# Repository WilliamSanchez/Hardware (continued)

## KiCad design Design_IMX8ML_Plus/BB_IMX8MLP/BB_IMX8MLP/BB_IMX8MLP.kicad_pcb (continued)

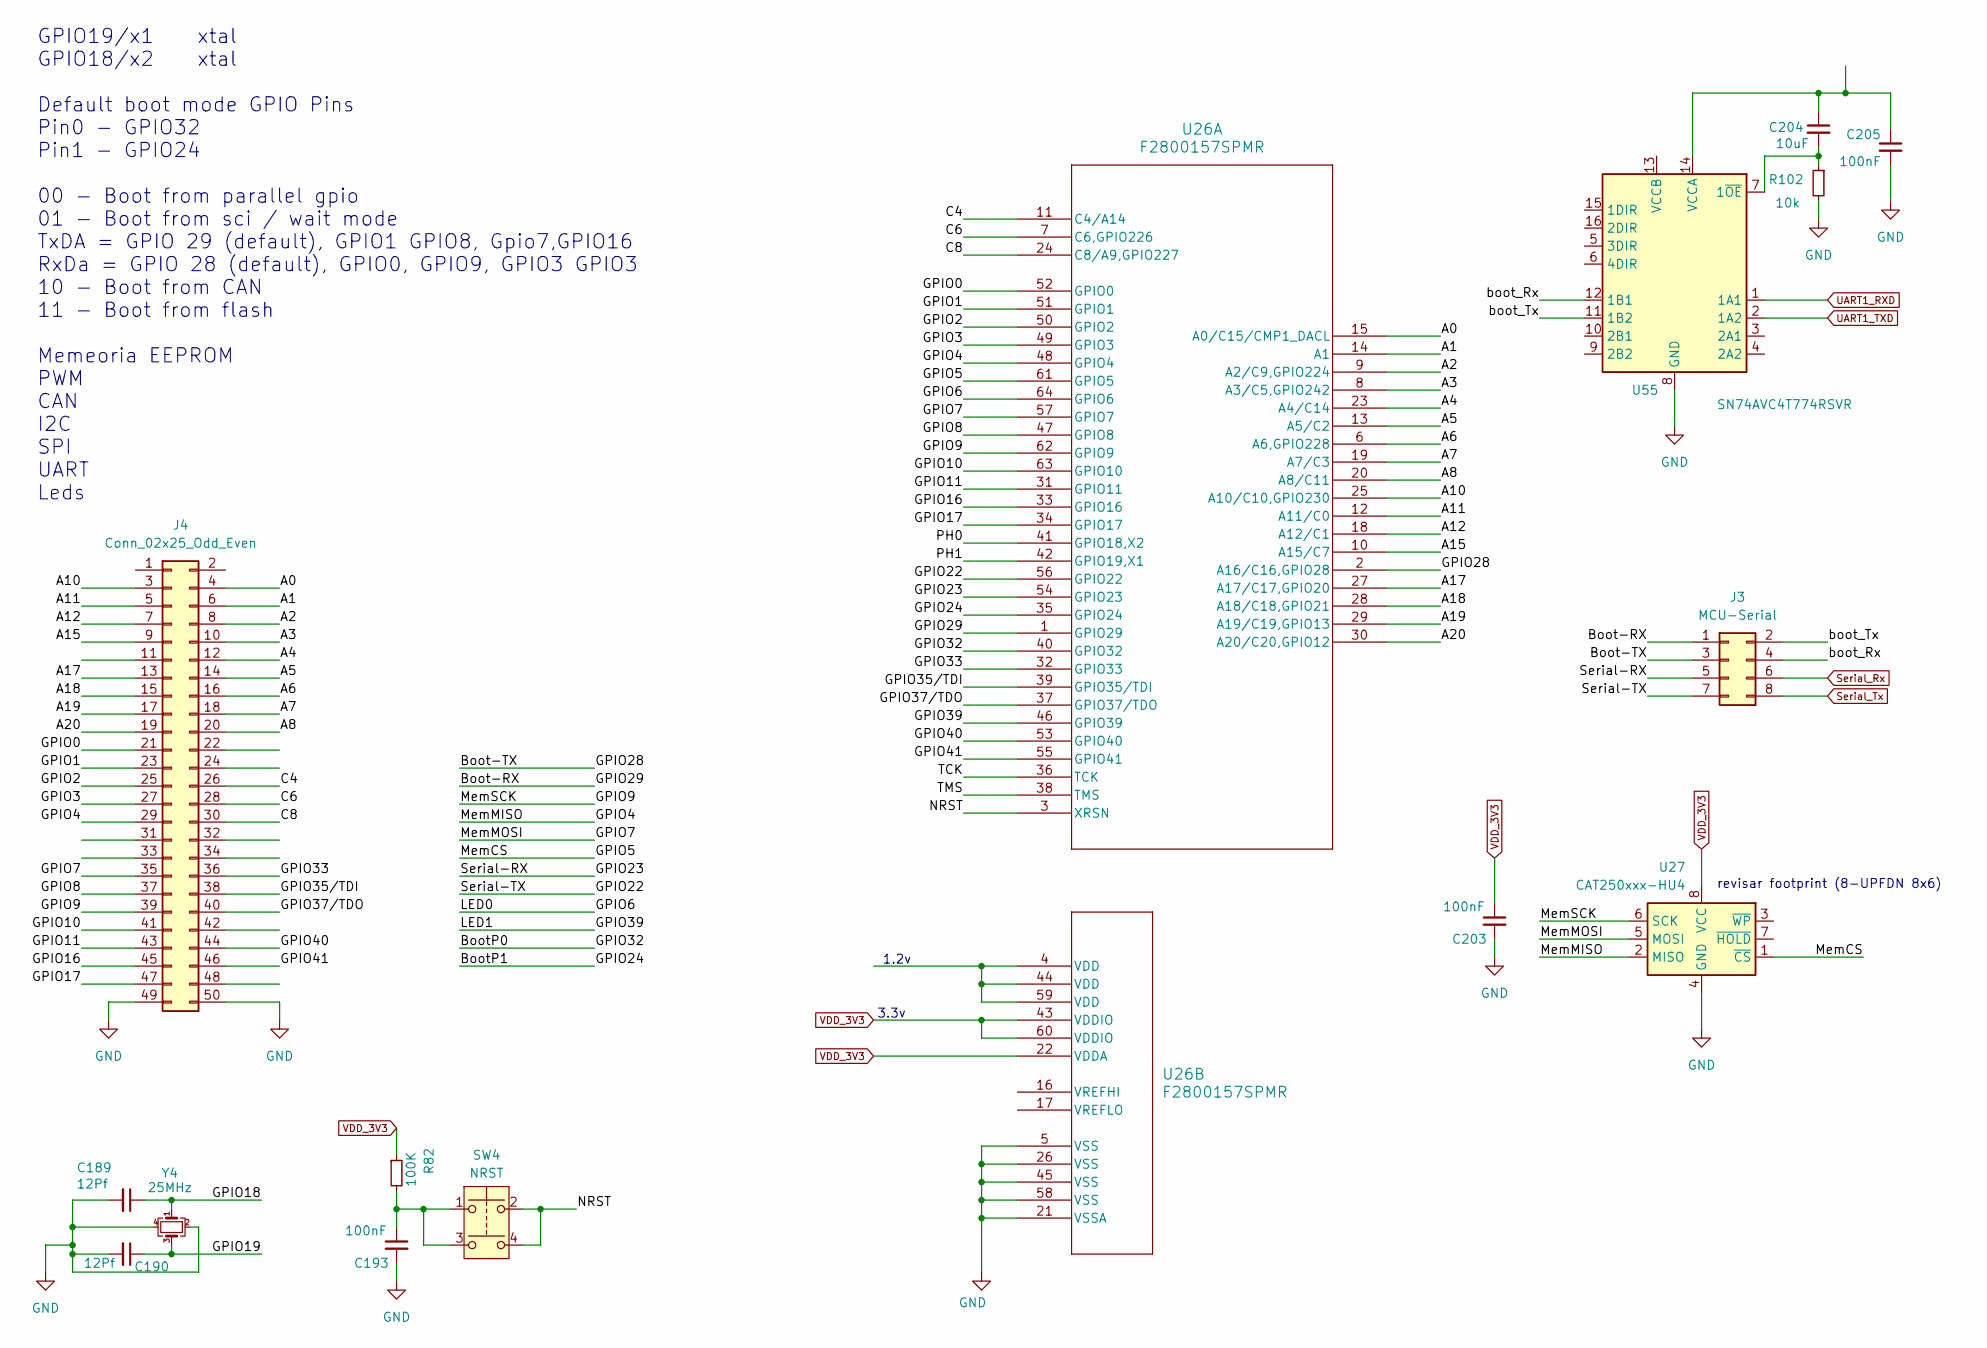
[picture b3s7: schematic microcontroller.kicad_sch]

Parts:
C189, C190: 12Pf; C_0402_1005Metric
C193, C203, C205: 100nF; C_0402_1005Metric
C204: 10uF; C_0402_1005Metric
J3: MCU-Serial; PinHeader_2x04_P2.54mm_Vertical
J4: Conn_02x25_Odd_Even; PinSocket_2x25_P2.54mm_Vertical
R82: 100K; R_0402_1005Metric
R102: 10k; R_0402_1005Metric
SW4: NRST; SW_SPST_TL3342
U26: F2800157SPMR; LQFP_00137PM_TEX
U27: CAT250xxx-HU4; DFN-8-1EP_3x2mm_P0.5mm_EP1.75x1.45mm
U55: SN74AVC4T774RSVR; UQFN-16_1.8x2.6mm_P0.4mm
Y4: 25MHz; Crystal_SMD_3225-4Pin_3.2x2.5mm

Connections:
/MCU/A0: J4.4, U26.15 (A0/C15/CMP1_DACL)
/MCU/A1: J4.6, U26.14 (A1)
/MCU/A2: J4.8, U26.9 (A2/C9,GPIO224)
/MCU/A3: J4.10, U26.8 (A3/C5,GPIO242)
/MCU/A4: J4.12, U26.23 (A4/C14)
/MCU/A5: J4.14, U26.13 (A5/C2)
/MCU/A6: J4.16, U26.6 (A6,GPIO228)
/MCU/A7: J4.18, U26.19 (A7/C3)
/MCU/A8: J4.20, U26.20 (A8/C11)
/MCU/A10: J4.3, U26.25 (A10/C10,GPIO230)
/MCU/A11: J4.5, U26.12 (A11/C0)
/MCU/A12: J4.7, U26.18 (A12/C1)
/MCU/A15: J4.9, U26.10 (A15/C7)
/MCU/A17: J4.13, U26.27 (A17/C17,GPIO20)
/MCU/A18: J4.15, U26.28 (A18/C18,GPIO21)
/MCU/A19: J4.17, U26.29 (A19/C19,GPIO13)
/MCU/A20: J4.19, U26.30 (A20/C20,GPIO12)
/MCU/Boot-RX: J3.1, U26.1 (GPIO29)
/MCU/Boot-TX: J3.3, U26.2 (A16/C16,GPIO28)
/MCU/BootP0: U26.40 (GPIO32)
/MCU/BootP1: U26.35 (GPIO24)
/MCU/C4: J4.26, U26.11 (C4/A14)
/MCU/C6: J4.28, U26.7 (C6,GPIO226)
/MCU/C8: J4.30, U26.24 (C8/A9,GPIO227)
/MCU/GPIO0: J4.21, U26.52 (GPIO0)
/MCU/GPIO1: J4.23, U26.51 (GPIO1)
/MCU/GPIO2: J4.25, U26.50 (GPIO2)
/MCU/GPIO3: J4.27, U26.49 (GPIO3)
/MCU/GPIO4: J4.29, U26.48 (GPIO4), U27.2 (MISO)
/MCU/GPIO5: U26.61 (GPIO5), U27.1 (~CS)
/MCU/GPIO6: U26.64 (GPIO6)
/MCU/GPIO7: J4.35, U26.57 (GPIO7), U27.5 (MOSI)
/MCU/GPIO8: J4.37, U26.47 (GPIO8)
/MCU/GPIO9: J4.39, U26.62 (GPIO9), U27.6 (SCK)
/MCU/GPIO10: J4.41, U26.63 (GPIO10)
/MCU/GPIO11: J4.43, U26.31 (GPIO11)
/MCU/GPIO16: J4.45, U26.33 (GPIO16)
/MCU/GPIO17: J4.47, U26.34 (GPIO17)
/MCU/GPIO18: C189.1, Y4.1
/MCU/GPIO19: C190.1, Y4.3
/MCU/GPIO22: J3.7, U26.56 (GPIO22)
/MCU/GPIO23: J3.5, U26.54 (GPIO23)
/MCU/GPIO33: J4.36, U26.32 (GPIO33)
/MCU/GPIO35/TDI: J4.38, U26.39 (GPIO35/TDI)
/MCU/GPIO37/TDO: J4.40, U26.37 (GPIO37/TDO)
/MCU/GPIO39: U26.46 (GPIO39)
/MCU/GPIO40: J4.44, U26.53 (GPIO40)
/MCU/GPIO41: J4.46, U26.55 (GPIO41)
/MCU/NRST: SW4.2, SW4.4, U26.3 (XRSN)
/MCU/PH0: U26.41 (GPIO18,X2)
/MCU/PH1: U26.42 (GPIO19,X1)
/MCU/TCK: U26.36 (TCK)
/MCU/TMS: U26.38 (TMS)
/MCU/boot_Rx: J3.4, U55.12 (1B1)
/MCU/boot_Tx: J3.2, U55.11 (1B2)
GND: C189.2, C190.2, C193.2, C203.2, C205.2, J4.49, J4.50, R102.2, U26.5 (VSS), U26.21 (VSSA), U26.26 (VSS), U26.45 (VSS), U26.58 (VSS), U27.4 (GND), U27.9 (GND), U55.8 (GND), Y4.2, Y4.4; also elsewhere on the board
unnamed: C193.1, R82.2, SW4.1, SW4.3
unnamed: U26.4 (VDD), U26.44 (VDD), U26.59 (VDD)
unnamed: C204.2, R102.1, U55.7 (1~OE)
unnamed: C204.1, C205.1, U55.14 (VCCA)
Serial_Rx: J3.6; also elsewhere on the board
Serial_Tx: J3.8; also elsewhere on the board
UART1_RXD: U55.1 (1A1); also elsewhere on the board
UART1_TXD: U55.2 (1A2); also elsewhere on the board
VDD_3V3: C203.1, R82.1, U26.22 (VDDA), U26.43 (VDDIO), U26.60 (VDDIO), U27.8 (VCC); also elsewhere on the board

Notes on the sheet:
revisar footprint (8-UPFDN 8x6)
3.3v
1.2v
GPIO19/x1 xtal GPIO18/x2 xtal Default boot mode GPIO Pins Pin0 - GPIO32 Pin1 - GPIO24 00 - Boot from parallel gpio 01 - Boot from sci / wait mode TxDA = GPIO 29 (default), GPIO1 GPIO8, Gpio7,GPIO16 RxDa = GPIO 28 (default), GPIO0, GPIO9, GPIO3 GPIO3 10 - Boot from CAN 11 - Boot from flash Memeoria 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

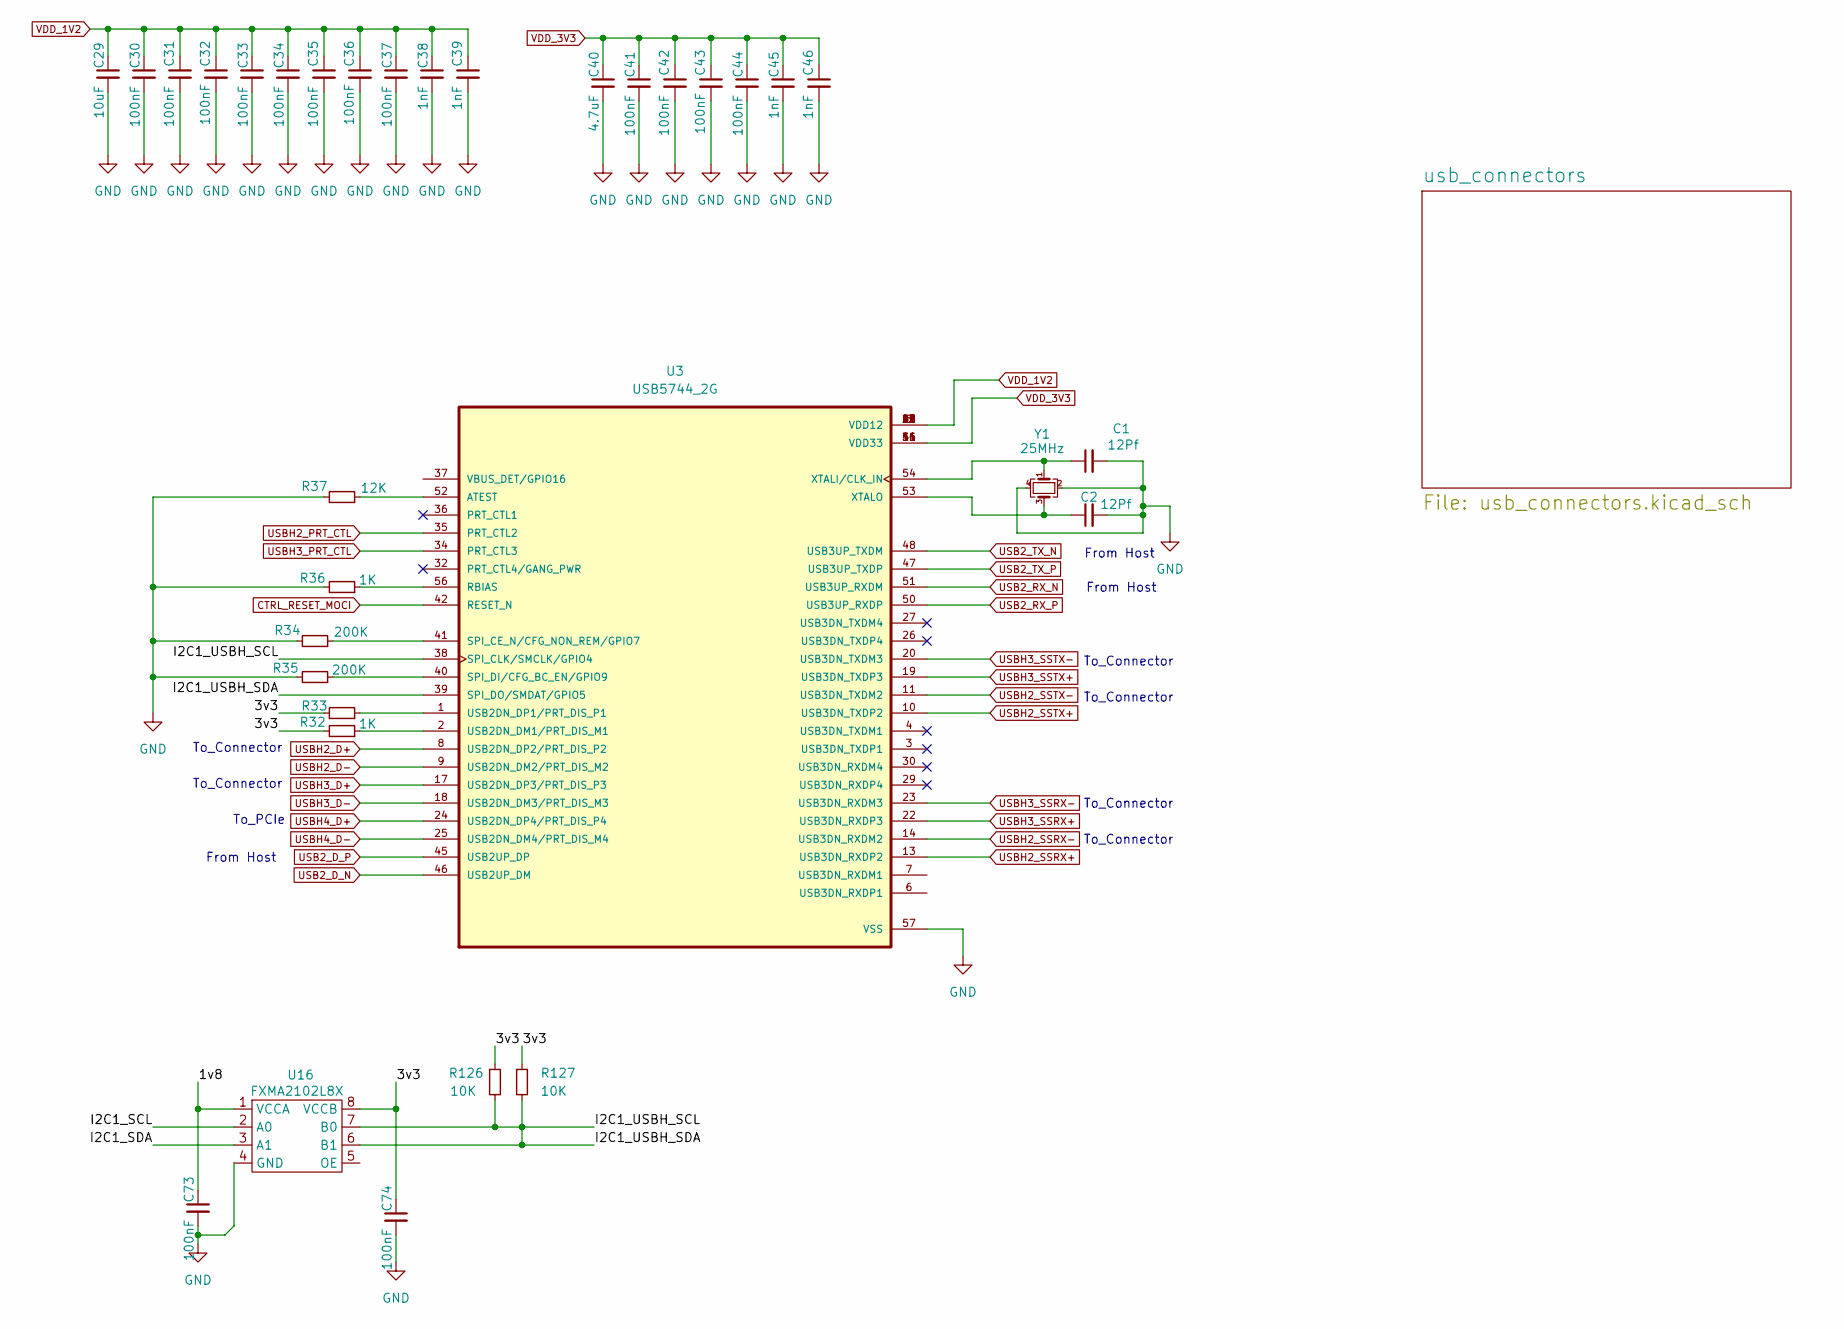
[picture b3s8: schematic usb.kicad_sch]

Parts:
C1, C2: 12Pf; C_0402_1005Metric
C29: 10uF; C_0402_1005Metric
C30, C31, C32, C33, C34, C35, C36, C37, C41, C42, C43, C44, C73, C74: 100nF; C_0402_1005Metric
C38, C39, C45, C46: 1nF; C_0402_1005Metric
C40: 4.7uF; C_0402_1005Metric
R32, R33, R36: 1K; R_0402_1005Metric
R34, R35: 200K; R_0402_1005Metric
R37: 12K; R_0402_1005Metric
R126, R127: 10K; R_0402_1005Metric
U3: USB5744_2G; QFN40P700X700X100-57N; PARTREV DS00001855E(02-10-17)
U16: FXMA2102L8X; MICROPAK8_1P6X1P6_ONS
Y1: 25MHz; Crystal_SMD_3225-4Pin_3.2x2.5mm

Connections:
/USB/1v8: C73.1, U16.1 (VCCA)
/USB/3v3: C74.1, R32.2, R33.2, R126.1, R127.1, U16.8 (VCCB)
/USB/I2C1_SCL: U16.2 (A0)
/USB/I2C1_SDA: U16.3 (A1)
/USB/I2C1_USBH_SCL: R126.2, R127.2, U3.38 (SPI_CLK/SMCLK/GPIO4), U3.39 (SPI_DO/SMDAT/GPIO5), U16.6 (B1), U16.7 (B0)
CTRL_RESET_MOCI: U3.42 (RESET_N); also elsewhere on the board
GND: C1.2, C2.2, C29.2, C30.2, C31.2, C32.2, C33.2, C34.2, C35.2, C36.2, C37.2, C38.2, C39.2, C40.2, C41.2, C42.2, C43.2, C44.2, C45.2, C46.2, C73.2, C74.2, R34.2, R35.2, R36.2, R37.2, U3.57 (VSS), U16.4 (GND), Y1.2, Y1.4; also elsewhere on the board
unnamed: R37.1, U3.52 (ATEST)
unnamed: R36.1, U3.56 (RBIAS)
unnamed: R34.1, U3.41 (SPI_CE_N/CFG_NON_REM/GPIO7)
unnamed: R35.1, U3.40 (SPI_DI/CFG_BC_EN/GPIO9)
unnamed: R32.1, U3.2 (USB2DN_DM1/PRT_DIS_M1)
unnamed: R33.1, U3.1 (USB2DN_DP1/PRT_DIS_P1)
unnamed: C1.1, U3.54 (XTALI/CLK_IN), Y1.1
unnamed: C2.1, U3.53 (XTALO), Y1.3
USB2_D_N: U3.46 (USB2UP_DM); also elsewhere on the board
USB2_D_P: U3.45 (USB2UP_DP); also elsewhere on the board
USB2_RX_N: U3.51 (USB3UP_RXDM); also elsewhere on the board
USB2_RX_P: U3.50 (USB3UP_RXDP); also elsewhere on the board
USB2_TX_N: U3.48 (USB3UP_TXDM); also elsewhere on the board
USB2_TX_P: U3.47 (USB3UP_TXDP); also elsewhere on the board
USBH2_D+: U3.8 (USB2DN_DP2/PRT_DIS_P2); also elsewhere on the board
USBH2_D-: U3.9 (USB2DN_DM2/PRT_DIS_M2); also elsewhere on the board
USBH2_PRT_CTL: U3.35 (PRT_CTL2); also elsewhere on the board
USBH2_SSRX+: U3.13 (USB3DN_RXDP2); also elsewhere on the board
USBH2_SSRX-: U3.14 (USB3DN_RXDM2); also elsewhere on the board
USBH2_SSTX+: U3.10 (USB3DN_TXDP2); also elsewhere on the board
USBH2_SSTX-: U3.11 (USB3DN_TXDM2); also elsewhere on the board
USBH3_D+: U3.17 (USB2DN_DP3/PRT_DIS_P3); also elsewhere on the board
USBH3_D-: U3.18 (USB2DN_DM3/PRT_DIS_M3); also elsewhere on the board
USBH3_PRT_CTL: U3.34 (PRT_CTL3); also elsewhere on the board
USBH3_SSRX+: U3.22 (USB3DN_RXDP3); also elsewhere on the board
USBH3_SSRX-: U3.23 (USB3DN_RXDM3); also elsewhere on the board
USBH3_SSTX+: U3.19 (USB3DN_TXDP3); also elsewhere on the board
USBH3_SSTX-: U3.20 (USB3DN_TXDM3); also elsewhere on the board
USBH4_D+: U3.24 (USB2DN_DP4/PRT_DIS_P4); also elsewhere on the board
USBH4_D-: U3.25 (USB2DN_DM4/PRT_DIS_M4); also elsewhere on the board
VDD_1V2: C29.1, C30.1, C31.1, C32.1, C33.1, C34.1, C35.1, C36.1, C37.1, C38.1, C39.1, U3.5 (VDD12), U3.12 (VDD12), U3.15 (VDD12), U3.21 (VDD12), U3.28 (VDD12), U3.33 (VDD12), U3.43 (VDD12), U3.49 (VDD12); also elsewhere on the board
VDD_3V3: C40.1, C41.1, C42.1, C43.1, C44.1, C45.1, C46.1, U3.16 (VDD33), U3.31 (VDD33), U3.44 (VDD33), U3.55 (VDD33); also elsewhere on the board

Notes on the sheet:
To_Connector
To_PCIe
From Host

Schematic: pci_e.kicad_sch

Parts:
C28, C77, C78, C156: 100nF; C_0402_1005Metric
C154, C201: 100pF; C_0402_1005Metric
C155: 1nF; C_0402_1005Metric
C200: 47uF; C_0402_1005Metric
C202: 22uF; C_0402_1005Metric
D2, D3, D4: GREEN; LED_0402_1005Metric
J8: Bus_PCI_Express_Mini; BUS_PCI_Express_Mini
J11: SIM_Card; nanoSIM_Hinged_CUI_NSIM-2-C
J22: SD_Card_Receptacle; SD_Hirose_DM1AA_SF_PEJ82
Q5: Q_Dual_NMOS_S1G1D2S2G2D1; SOT-563
R24, R25, R26, R118, R119: 100K; R_0402_1005Metric
R62, R63, R121: 10K; R_0402_1005Metric
R100, R101: 150K; R_0402_1005Metric
R117: 47K; R_0402_1005Metric
R120: 4.7K; R_0402_1005Metric
U18: FXMA2102L8X; MICROPAK8_1P6X1P6_ONS
U54: SC4215A; SOIC-8-1EP_3.9x4.9mm_P1.27mm_EP2.41x3.81mm

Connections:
/PCIe_SDCard/1V5_PCIe: C201.1, C202.1, J8.6 (+1V5), J8.28 (+1V5), J8.48 (+1V5), R100.1, U54.6 (V_OUT)
/PCIe_SDCard/1v8: C77.1, C200.1, R120.1, U18.1 (VCCA), U54.3 (V_IN)
/PCIe_SDCard/3V3_PCIe: J8.2 (+3V3AUX), J8.24 (+3V3AUX), J8.39 (+3V3AUX), J8.41 (+3V3AUX), J8.52 (+3V3AUX), R24.1, R25.1, R26.1, R117.1
/PCIe_SDCard/3v3: C78.1, R62.1, R63.1, U18.8 (VCCB)
/PCIe_SDCard/CLK: J8.12 (UIM_CLK), J11.3 (CLK)
/PCIe_SDCard/I/O: J8.10 (UIM_DATA), J11.7 (I/O)
/PCIe_SDCard/PCIe_CLK: J8.30 (SMB_CLK), R62.2, U18.6 (B1)
/PCIe_SDCard/PCIe_PowerEnable: U18.5 (OE)
/PCIe_SDCard/PCIe_SDA: J8.32 (SMB_DATA), R63.2, U18.7 (B0)
/PCIe_SDCard/PRSET#: J8.22 (~PERST), Q5.3 (D), R121.2
/PCIe_SDCard/RST: J8.14 (~UIM_RESET), J11.2 (RST)
/PCIe_SDCard/VCC: C28.1, J8.8 (UIM_PWR), J11.1 (VCC)
/PCIe_SDCard/VPP: J8.16 (UIM_VPP), J11.6 (VPP)
/PCIe_SDCard/W_DISABLE#: J8.20 (~W_DISABLE), R117.2
GND: C28.2, C77.2, C78.2, C154.2, C155.2, C156.2, C200.2, C201.2, C202.2, J8.4 (GND), J8.9 (GND), J8.15 (GND), J8.18 (GND), J8.21 (GND), J8.26 (GND), J8.27 (GND), J8.29 (GND), J8.34 (GND), J8.35 (GND), J8.37 (GND), J8.40 (GND), J8.43 (GND), J8.50 (GND), J11.5 (GND), J22.3 (VSS), J22.6 (VSS), Q5.1 (S), Q5.4 (S), R101.2, R118.2, U18.4 (GND), U54.8 (GND), U54.9 (PAD); also elsewhere on the board
I2C1_SCL: U18.3 (A1); also elsewhere on the board
I2C1_SDA: U18.2 (A0); also elsewhere on the board
unnamed: D2.2 (A), R24.2
unnamed: D2.1 (K), J8.46 (~LED_WPAN)
unnamed: D3.2 (A), R25.2
unnamed: D3.1 (K), J8.44 (~LED_WLAN)
unnamed: D4.2 (A), R26.2
unnamed: D4.1 (K), J8.42 (~LED_WWAN)
unnamed: Q5.5 (G), Q5.6 (D), R119.2
unnamed: R100.2, R101.1, U54.7 (FB)
PCIE_REF_PAD_CLK_N: J8.11 (REFCLK-); also elsewhere on the board
PCIE_REF_PAD_CLK_P: J8.13 (REFCLK+); also elsewhere on the board
PCIE_RXN_N: J8.23 (PERn0); also elsewhere on the board
PCIE_RXN_P: J8.25 (PERp0); also elsewhere on the board
PCIE_TXN_N: J8.31 (PETn0); also elsewhere on the board
PCIE_TXN_P: J8.33 (PETp0); also elsewhere on the board
PCIe_RESET#: Q5.2 (G), R118.1
PCIe_WAKE#: J8.1 (~WAKE), R120.2
SDC2_CLK: J22.5 (CLK); also elsewhere on the board
SDC2_CMD: J22.2 (CMD); also elsewhere on the board
SDC2_DATA0: J22.7 (DAT0); also elsewhere on the board
SDC2_DATA1: J22.8 (DAT1); also elsewhere on the board
SDC2_DATA2: J22.9 (DAT2); also elsewhere on the board
SDC2_DATA3: J22.1 (CD/DAT3); also elsewhere on the board
USBH4_D+: J8.38 (USB_D+); also elsewhere on the board
USBH4_D-: J8.36 (USB_D-); also elsewhere on the board
VDD_3V3: C154.1, C155.1, C156.1, J22.4 (VDD), R119.1, R121.1; also elsewhere on the board

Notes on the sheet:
Revisar footprint

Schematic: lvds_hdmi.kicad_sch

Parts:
C63, C105: 100nF; C_0402_1005Metric
J7: HDMI_A; HDMI_A_Molex_208658-1001_Horizontal
J17: LVDS; Hirose_FH12-40S-0.5SH_1x40-1MP_P0.50mm_Horizontal
R88, R90: 10K; R_0402_1005Metric
R89, R91: 10k; R_0402_1005Metric
U2, U37: PCMF2HDMI2SZ; WLCSP10_4-2-4_NEX
U41: FXMA2102L8X; MICROPAK8_1P6X1P6_ONS

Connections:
/LVDS_HDMI/1v8: C63.1, R88.1, R89.1, U41.1 (VCCA)
/LVDS_HDMI/5v5: C105.1, J7.18 (+5V), R90.1, R91.1, U41.5 (OE), U41.8 (VCCB)
/LVDS_HDMI/EN_LVDS: J17.24
/LVDS_HDMI/I2C1_HDMI_SCL_CON: J7.15 (SCL), U41.7 (B0)
/LVDS_HDMI/I2C1_HDMI_SDA_CON: J7.16 (SDA), R90.2, R91.2, U41.6 (B1)
/LVDS_HDMI/PWM_LVDS: J17.23
/LVDS_HDMI/TOUCH_INT1#: J17.20
/LVDS_HDMI/TOUCH_RESET_T1#: J17.21
GND: C63.2, C105.2, J7.2 (D2S), J7.5 (D1S), J7.8 (D0S), J7.11 (CKS), J7.17 (GND), J7.SH, J17.3, J17.6, J17.9, J17.12, J17.15, J17.16, J17.19, J17.22, J17.25, J17.28, J17.31, U41.4 (GND); also elsewhere on the board
HDMI_DDC_SCL: R88.2, U41.3 (A1); also elsewhere on the board
HDMI_DDC_SDA: R89.2, U41.2 (A0); also elsewhere on the board
HDMI_TX0_N: U37.A3 (CH2_IN+); also elsewhere on the board
HDMI_TX0_P: U37.A4 (CH2_IN-); also elsewhere on the board
HDMI_TX1_N: U2.A1 (CH1_IN+); also elsewhere on the board
HDMI_TX1_P: U2.A2 (CH1_IN-); also elsewhere on the board
HDMI_TX2_N: U2.A3 (CH2_IN+); also elsewhere on the board
HDMI_TX2_P: U2.A4 (CH2_IN-); also elsewhere on the board
HDMI_TXC_N: U37.A1 (CH1_IN+); also elsewhere on the board
HDMI_TXC_P: U37.A2 (CH1_IN-); also elsewhere on the board
I2C1_SCL: J17.17; also elsewhere on the board
I2C1_SDA: J17.18; also elsewhere on the board
LVDS0_CLK_N: J17.8; also elsewhere on the board
LVDS0_CLK_P: J17.7; also elsewhere on the board
LVDS0_D0_N: J17.2; also elsewhere on the board
LVDS0_D0_P: J17.1; also elsewhere on the board
LVDS0_D1_N: J17.5; also elsewhere on the board
LVDS0_D1_P: J17.4; also elsewhere on the board
LVDS0_D2_N: J17.11; also elsewhere on the board
LVDS0_D2_P: J17.10; also elsewhere on the board
LVDS0_D3_N: J17.14; also elsewhere on the board
LVDS0_D3_P: J17.13; also elsewhere on the board
LVDS1_CLK_N: J17.33; also elsewhere on the board
LVDS1_CLK_P: J17.32; also elsewhere on the board
LVDS1_D0_N: J17.27; also elsewhere on the board
LVDS1_D0_P: J17.26; also elsewhere on the board
LVDS1_D1_N: J17.30; also elsewhere on the board
LVDS1_D1_P: J17.29; also elsewhere on the board
LVDS1_D2_N: J17.36; also elsewhere on the board
LVDS1_D2_P: J17.35; also elsewhere on the board
LVDS1_D3_N: J17.39; also elsewhere on the board
LVDS1_D3_P: J17.38; also elsewhere on the board
unnamed: J7.10 (CK+), U37.C2 (CH1_OUT-)
unnamed: J7.12 (CK-), U37.C1 (CH1_OUT+)
unnamed: J7.7 (D0+), U37.C4 (CH2_OUT-)
unnamed: J7.9 (D0-), U37.C3 (CH2_OUT+)
unnamed: J7.4 (D1+), U2.C2 (CH1_OUT-)
unnamed: J7.6 (D1-), U2.C1 (CH1_OUT+)
unnamed: J7.1 (D2+), U2.C4 (CH2_OUT-)
unnamed: J7.3 (D2-), U2.C3 (CH2_OUT+)

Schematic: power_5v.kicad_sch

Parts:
C3, C7, C8, C9: 47uF; C_0805_2012Metric
C17: 4.7uF; C_0603_1608Metric
C18, C19, C75, C76, C101, C102: 100nF; C_0402_1005Metric
C139, C188: 10uF; C_1210_3225Metric
D11: GREEN; LED_0402_1005Metric
L1: 2.2uH_12A; IND_PA4342.222NLT
R1, R2: 10; R_0402_1005Metric
R3, R6, R9, R129: 100K; R_0402_1005Metric
R4: 47K; R_0402_1005Metric
R5: 8.87K; R_0402_1005Metric
R8: 510K; R_0402_1005Metric
R79: 0.01; R_1206_3216Metric
R111: 1K; R_0402_1005Metric
R124, R125: 10K; R_0402_1005Metric
U5: AOZ2261AQI-15; QFN4X4-22L_EP2_S_AOS
U17: FXMA2102L8X; MICROPAK8_1P6X1P6_ONS
U20: INA219BxD; SOT-23-8

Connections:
5V_BB: C3.1, C7.1, C8.1, C9.1, L1.1, R2.2, R4.1, R79.1, R111.1; also elsewhere on the board
+V5_STB: R129.1; also elsewhere on the board
+V_SUPPLY_FILT: C139.1, C188.1, R8.1, U5.7 (IN), U5.8 (IN), U5.9 (IN); also elsewhere on the board
/power_unit/power_5v/1v8: C75.1, U17.1 (VCCA)
/power_unit/power_5v/3v3: C76.1, C101.1, R124.1, R125.1, U17.8 (VCCB), U20.5 (VS)
/power_unit/power_5v/+V_STB: C17.1, R9.1, U5.21 (VCC)
/power_unit/power_5v/FB_5V: R4.2, R5.1, U5.5 (FB)
/power_unit/power_5v/INA_SCL: R124.2, U17.7 (B0), U20.4 (SCL)
/power_unit/power_5v/INA_SDA: R125.2, U17.6 (B1), U20.3 (SDA)
GND: C3.2, C7.2, C8.2, C9.2, C17.2, C19.2, C75.2, C76.2, C101.2, C139.2, C188.2, D11.1 (K), R3.2, R5.2, R6.2, U5.4 (AGND), U5.12 (PGND), U5.13 (PGND), U5.14 (PGND), U5.15 (PGND), U5.19 (PGND), U17.4 (GND), U20.6 (GND); also elsewhere on the board
I2C1_SCL: U17.2 (A0); also elsewhere on the board
I2C1_SDA: U17.3 (A1); also elsewhere on the board
unnamed: C18.2, L1.2, U5.10 (LX), U5.11 (LX), U5.16 (LX), U5.17 (LX), U5.18 (LX)
unnamed: D11.2 (A), R111.2
unnamed: R6.1, R129.2, U5.3 (*PFM)
unnamed: C19.1, U5.22 (SS)
unnamed: R8.2, U5.6 (TON)
unnamed: C18.1, U5.20 (BST)
unnamed: R9.2, U5.1 (PGOOD)
unnamed: C102.1, R2.1, U20.8 (IN+)
unnamed: C102.2, R1.1, U20.7 (IN-)
PMIC_EN_5V: R3.1, U5.2 (EN); also elsewhere on the board
VDD_SYS: R1.2, R79.2; also elsewhere on the board

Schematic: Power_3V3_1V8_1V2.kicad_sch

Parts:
C21, C22, C23, C24: 47uF; C_0805_2012Metric
C25: 4.7uF; C_0603_1608Metric
C26, C27: 100nF; C_0402_1005Metric
C67, C69, C70: 22uF; C_0805_2012Metric
C68, C71: 100pF; C_0402_1005Metric
C72: 22uF; C_0402_1005Metric
D12, D15, D16: GREEN; LED_0402_1005Metric
L2: 1.5uH_16A; IND_PA4342.222NLT
L3: 2.2uH_4A; IND_SRP4020TA-1R0M_BRN
L4: 2.2uH_4.8A; IND_SRP4020TA-1R0M_BRN
Q4: NTZD3154NT1G; SOT-563
R18, R21, R23, R114, R115, R128: 100K; R_0402_1005Metric
R19: 47K; R_0402_1005Metric
R20: 15K; R_0402_1005Metric
R22: 510K; R_0402_1005Metric
R28: 330K; R_0402_1005Metric
R29, R30, R31: 150K; R_0402_1005Metric
R112, R113, R116: 1K; R_0402_1005Metric
U7: AOZ2261AQI-15; QFN4X4-22L_EP2_S_AOS
U14, U15: PAM2310BECADJR; SOIC-8-1EP_3.9x4.9mm_P1.27mm_EP2.41x3.81mm

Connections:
+V5_STB: R18.1, R128.1, U7.2 (EN); also elsewhere on the board
+V_SUPPLY_FILT: R22.1, U7.7 (IN), U7.8 (IN), U7.9 (IN); also elsewhere on the board
/power_unit/power_3V3_1V8_1V2/+V_STB: C25.1, R23.1, U7.21 (VCC)
/power_unit/power_3V3_1V8_1V2/FB_5V: R19.2, R20.1, U7.5 (FB)
/power_unit/power_3V3_1V8_1V2/SW_1v2: L3.1, L4.1, U14.3 (SW), U15.3 (SW)
GND: C21.2, C22.2, C23.2, C24.2, C25.2, C27.2, C67.2, C69.2, C70.2, C72.2, D12.1 (K), Q4.1 (S), Q4.4 (S), R18.2, R20.2, R21.2, R29.2, R31.2, R114.2, R115.2, U7.4 (AGND), U7.12 (PGND), U7.13 (PGND), U7.14 (PGND), U7.15 (PGND), U7.19 (PGND), U14.4 (GND), U15.4 (GND); also elsewhere on the board
unnamed: C26.2, L2.2, U7.10 (LX), U7.11 (LX), U7.16 (LX), U7.17 (LX), U7.18 (LX)
unnamed: D12.2 (A), R112.2
unnamed: D15.2 (A), R113.2
unnamed: D15.1 (K), Q4.6 (D)
unnamed: D16.2 (A), R116.2
unnamed: D16.1 (K), Q4.3 (D)
unnamed: R21.1, R128.2, U7.3 (*PFM)
unnamed: C27.1, U7.22 (SS)
unnamed: R22.2, U7.6 (TON)
unnamed: C26.1, U7.20 (BST)
unnamed: R23.2, U7.1 (PGOOD)
unnamed: C68.2, R28.2, R29.1, U14.5 (FB)
unnamed: C71.2, R30.2, R31.1, U15.5 (FB)
VDD_1V2: C71.1, C72.1, L4.2, Q4.2 (G), R30.1, R114.1; also elsewhere on the board
VDD_1V8: C68.1, C69.1, L3.2, Q4.5 (G), R28.1, R115.1; also elsewhere on the board
VDD_3V3: C21.1, C22.1, C23.1, C24.1, C67.1, C70.1, L2.1, R19.1, R112.1, R113.1, R116.1, U14.2 (VIN), U14.7 (EN), U15.2 (VIN), U15.7 (EN); also elsewhere on the board

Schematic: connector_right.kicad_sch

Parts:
J1: DF40C-80DP-0.4V_51_; HRS_DF40C-80DP-0.4V_51_
J2: Front_Right; HRS_DF40C-100DP-0.4V_51_; PARTREV 8

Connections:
BOOT_MODE0: J1.33; also elsewhere on the board
BOOT_MODE1: J1.35; also elsewhere on the board
BOOT_MODE2: J1.37; also elsewhere on the board
BOOT_MODE3: J1.39; also elsewhere on the board
CSI1_CLK_N: J2.18; also elsewhere on the board
CSI1_CLK_P: J2.20; also elsewhere on the board
CSI1_D0_N: J2.32; also elsewhere on the board
CSI1_D0_P: J2.30; also elsewhere on the board
CSI1_D1_N: J2.26; also elsewhere on the board
CSI1_D1_P: J2.24; also elsewhere on the board
CSI1_D2_N: J2.14; also elsewhere on the board
CSI1_D2_P: J2.12; also elsewhere on the board
CSI1_D3_N: J2.8; also elsewhere on the board
CSI1_D3_P: J2.6; also elsewhere on the board
CSI2_CLK_N: J2.54; also elsewhere on the board
CSI2_CLK_P: J2.52; also elsewhere on the board
CSI2_D0_N: J2.42; also elsewhere on the board
CSI2_D0_P: J2.40; also elsewhere on the board
CSI2_D1_N: J2.48; also elsewhere on the board
CSI2_D1_P: J2.46; also elsewhere on the board
CSI2_D2_N: J2.60; also elsewhere on the board
CSI2_D2_P: J2.58; also elsewhere on the board
CSI2_D3_N: J2.66; also elsewhere on the board
CSI2_D3_P: J2.64; also elsewhere on the board
CTRL_RESET_MOCI: J2.89; also elsewhere on the board
DSI1_CLK_N: J2.84; also elsewhere on the board
DSI1_CLK_P: J2.82; also elsewhere on the board
DSI1_D0_N: J2.96; also elsewhere on the board
DSI1_D0_P: J2.94; also elsewhere on the board
DSI1_D1_N: J2.90; also elsewhere on the board
DSI1_D1_P: J2.88; also elsewhere on the board
DSI1_D2_N: J2.78; also elsewhere on the board
DSI1_D2_P: J2.76; also elsewhere on the board
DSI1_D3_N: J2.72; also elsewhere on the board
DSI1_D3_P: J2.70; also elsewhere on the board
GPIO1_IO00: J1.80
GPIO1_IO01: J1.78
GPIO1_IO05: J1.70
GPIO1_IO06: J1.68
GPIO1_IO07: J1.66
GPIO1_IO08: J1.64
GPIO1_IO09: J1.62
GPIO1_IO10: J1.60
GPIO1_IO11: J1.58
GPIO1_IO12: J1.56
GPIO1_IO13: J1.54
GPIO1_IO14: J1.52
GPIO1_IO15: J1.50
JTAG_MOD: J1.19
JTAG_TCK: J1.21; also elsewhere on the board
JTAG_TDI: J1.23; also elsewhere on the board
JTAG_TDO: J1.25; also elsewhere on the board
JTAG_TMS: J1.27; also elsewhere on the board
LVDS0_CLK_N: J2.59; also elsewhere on the board
LVDS0_CLK_P: J2.61; also elsewhere on the board
LVDS0_D0_N: J2.71; also elsewhere on the board
LVDS0_D0_P: J2.73; also elsewhere on the board
LVDS0_D1_N: J2.65; also elsewhere on the board
LVDS0_D1_P: J2.67; also elsewhere on the board
LVDS0_D2_N: J2.53; also elsewhere on the board
LVDS0_D2_P: J2.55; also elsewhere on the board
LVDS0_D3_N: J2.47; also elsewhere on the board
LVDS0_D3_P: J2.49; also elsewhere on the board
LVDS1_CLK_N: J2.23; also elsewhere on the board
LVDS1_CLK_P: J2.25; also elsewhere on the board
LVDS1_D0_N: J2.35; also elsewhere on the board
LVDS1_D0_P: J2.37; also elsewhere on the board
LVDS1_D1_N: J2.29; also elsewhere on the board
LVDS1_D1_P: J2.31; also elsewhere on the board
LVDS1_D2_N: J2.17; also elsewhere on the board
LVDS1_D2_P: J2.19; also elsewhere on the board
LVDS1_D3_N: J2.11; also elsewhere on the board
LVDS1_D3_P: J2.13; also elsewhere on the board
ON/OFF: J2.85; also elsewhere on the board
PCIE_REF_PAD_CLK_N: J1.12; also elsewhere on the board
PCIE_REF_PAD_CLK_P: J1.10; also elsewhere on the board
PCIE_RXN_N: J1.24; also elsewhere on the board
PCIE_RXN_P: J1.22; also elsewhere on the board
PCIE_TXN_N: J1.18; also elsewhere on the board
PCIE_TXN_P: J1.16; also elsewhere on the board
PMIC_RST_B: J2.87; also elsewhere on the board
USB1_D_N: J1.46; also elsewhere on the board
USB1_D_P: J1.44; also elsewhere on the board
USB1_RX_N: J1.40; also elsewhere on the board
USB1_RX_P: J1.38; also elsewhere on the board
USB1_TX_N: J1.34; also elsewhere on the board
USB1_TX_P: J1.32; also elsewhere on the board
USB1_VBUS: J1.28
USB2_D_N: J1.57; also elsewhere on the board
USB2_D_P: J1.55; also elsewhere on the board
USB2_RX_N: J1.51; also elsewhere on the board
USB2_RX_P: J1.49; also elsewhere on the board
USB2_TX_N: J1.45; also elsewhere on the board
USB2_TX_P: J1.43; also elsewhere on the board
USB2_VBUS: J1.61

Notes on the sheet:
GPIO_6_CSI
PWM_2
CSI_1_MCLK
USB_1_OC#
GPIO_5_CSI
USB_2_EN
USB_1_EN
ON/OFF Processor POR_B PMIC/Processor PMIC_RST_B PMIC PMIC_ON_REQ PMIC/Processor WDOG_B PMIC/Processor

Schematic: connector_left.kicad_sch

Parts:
C62: 22uF; C_0402_1005Metric
C103, C104, C106, C107, C108: 4,7uF; C_0402_1005Metric
J26: DF40C-80DP-0.4V_51_; HRS_DF40C-80DP-0.4V_51_
J31: Front_Right; HRS_DF40C-100DP-0.4V_51_; PARTREV 8

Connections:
EARC_AUX: J26.3
EARC_N_HPD: J26.5
EARC_P_UTIL: J26.7
ECSPI1_MISO: J31.70
ECSPI1_MOSI: J31.72
ECSPI1_SCLK: J31.74
ECSPI1_SSO: J31.76
ECSPI2_MISO: J31.78
ECSPI2_MOSI: J31.80
ECSPI2_SCLK: J31.82
ECSPI2_SSO: J31.84
ENET_MDC: J26.55; also elsewhere on the board
ENET_MDIO: J26.57; also elsewhere on the board
ENET_RD0: J26.45; also elsewhere on the board
ENET_RD1: J26.43; also elsewhere on the board
ENET_RD2: J26.41; also elsewhere on the board
ENET_RD3: J26.39; also elsewhere on the board
ENET_TD0: J26.27; also elsewhere on the board
ENET_TD1: J26.29; also elsewhere on the board
ENET_TD2: J26.31; also elsewhere on the board
ENET_TD3: J26.33; also elsewhere on the board
ETH1_LED1: J31.67; also elsewhere on the board
ETH1_LED2: J31.69; also elsewhere on the board
ETH1_MDI0+: J31.93; also elsewhere on the board
ETH1_MDI0-: J31.91; also elsewhere on the board
ETH1_MDI1+: J31.87; also elsewhere on the board
ETH1_MDI1-: J31.85; also elsewhere on the board
ETH1_MDI2+: J31.81; also elsewhere on the board
ETH1_MDI2-: J31.79; also elsewhere on the board
ETH1_MDI3+: J31.75; also elsewhere on the board
ETH1_MDI3-: J31.73; also elsewhere on the board
GND: C62.2, C103.2, C104.2, C106.2, C107.2, C108.2, J26.59, J26.60, J26.61, J26.62, J26.63, J26.64, J26.65, J26.66, J26.67, J26.68; also elsewhere on the board
HDMI_CEC: J31.22
HDMI_DDC_SCL: J31.8; also elsewhere on the board
HDMI_DDC_SDA: J31.10; also elsewhere on the board
HDMI_HPD: J31.20
HDMI_TX0_N: J31.26; also elsewhere on the board
HDMI_TX0_P: J31.28; also elsewhere on the board
HDMI_TX1_N: J31.32; also elsewhere on the board
HDMI_TX1_P: J31.34; also elsewhere on the board
HDMI_TX2_N: J31.38; also elsewhere on the board
HDMI_TX2_P: J31.40; also elsewhere on the board
HDMI_TXC_N: J31.14; also elsewhere on the board
HDMI_TXC_P: J31.16; also elsewhere on the board
I2C1_SCL: J26.18; also elsewhere on the board
I2C1_SDA: J26.20; also elsewhere on the board
I2C2_SCL: J26.30
I2C2_SDA: J26.32
I2C3_SCL: J26.26
I2C3_SDA: J26.24
I2C4_SCL: J26.38
I2C4_SDA: J26.36
SAI1_MCLK: J26.2; also elsewhere on the board
SAI1_RXC: J26.4
SAI1_RXD0: J26.13; also elsewhere on the board
SAI1_RXD1: J26.11
SAI1_RXFS: J26.6
SAI1_TXC: J26.49
SAI1_TXD4: J26.37
SAI1_TXD5: J26.35
SAI1_TXD6: J26.23
SAI1_TXD7: J26.17
SAI1_TXFS: J26.10
SAI2_MCLK: J31.21
SAI2_RXC: J31.23
SAI2_RXD0: J31.33
SAI2_RXFS: J31.25
SAI2_TXC: J31.27
SAI2_TXD0: J31.35
SAI2_TXFS: J31.29
SAI3_MCLK: J31.5
SAI3_RXC: J31.7
SAI3_RXD: J31.9
SAI3_RXFS: J31.11
SAI3_TXC: J31.13
SAI3_TXD: J31.15
SAI3_TXFS: J31.17
SAI5_MCLK: J31.51; also elsewhere on the board
SAI5_RXC: J31.41
SAI5_RXD0: J31.43
SAI5_RXD1: J31.45; also elsewhere on the board
SAI5_RXD2: J31.47
SAI5_RXD3: J31.49
SAI5_RXFS: J31.53; also elsewhere on the board
SDC1_RESET_B: J31.55
SDC2_CD_B: J31.54
SDC2_CLK: J31.46; also elsewhere on the board
SDC2_CMD: J31.48; also elsewhere on the board
SDC2_DATA0: J31.52; also elsewhere on the board
SDC2_DATA1: J31.50; also elsewhere on the board
SDC2_DATA2: J31.56; also elsewhere on the board
SDC2_DATA3: J31.58; also elsewhere on the board
SDC2_RESET_B: J31.60
SDC2_WP: J31.62
UART1_RXD: J26.46; also elsewhere on the board
UART1_TXD: J26.44; also elsewhere on the board
UART2_RXD: J26.40; also elsewhere on the board
UART2_TXD: J26.42; also elsewhere on the board
UART4_RXD: J26.48; also elsewhere on the board
UART4_TXD: J26.50; also elsewhere on the board
VDD_SYS: C62.1, C103.1, C104.1, C106.1, C107.1, C108.1, J26.69, J26.70, J26.71, J26.72, J26.73, J26.74, J26.75, J26.76, J26.77, J26.78, J26.79, J26.80; also elsewhere on the board

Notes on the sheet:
CAN1_TX
ETH_2_RGMII_RXD_2
CAN1_RX
ETH_2_RGMII_INT#
PCIe_1_RESET#
GPIO_7_CSI
I2S_1_MCLK
ETH_2_RGMII_RXD_3
UART_1_RTS
ETH_2_RGMII_RXD_0
ETH_2_RGMII_MDC
SD1_PWR_EN
CTRL_WAKE1_MICO#
I2S_2_BCLK
ETH_2_RGMII_RXD_1
I2S_1_D_IN
UART_1_CTS
ETH_2_RGMII_TX_CTL
GPIO_9_DSI
ETH_2_RGMII_MDIO
I2S_1_SYNC
I2S_2_D_OUT
ETH_2_RGMII_RX_CTL
ETH_2_RGMII_TXD_1
ETH_2_RGMII_TXD_2
ETH_2_RGMII_TXD_0
I2S_2_D_IN
GPIO_10_DSI
ETH_2_RGMII_TXD_3
CAN2_RX
UsB_2_OC#
CAN2_TX
ETH_2_RGMII_TX_TXC
I2S_1_D_OUT
I2S_1_BCLK
GPIO_8_CSI
ETH_2_RGMII_RX_RXC
PWM_3_DSI
I2S_2_SYNC
USB_1_ID

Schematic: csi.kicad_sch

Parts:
C79, C80, C196, C197: 100nF; C_0402_1005Metric
J12: CAM_1; 687124182122
J13: CAM_2; 687124182122
L7, L8, L9, L10, L11, L12, L13, L14, L15, L16: 12R@100MHz; FIL_EXC-14CH120U
R64, R65, R66, R67, R92, R93, R94, R95: 10K; R_0402_1005Metric
U19, U23, U44, U46, U47, U48: D3V3F4U10LP-7; DFN10_U-DFN2510-10_DIO
U45, U51: FXMA2102L8X; MICROPAK8_1P6X1P6_ONS
U53: SN74AVC4T774RSVR; UQFN-16_1.8x2.6mm_P0.4mm

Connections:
/CSI_DSI/CSI/1v8: C79.1, C196.1, R66.1, R67.1, R94.1, R95.1, U45.1 (VCCA), U51.1 (VCCA)
/CSI_DSI/CSI/3v3: C80.1, C197.1, R64.1, R65.1, R92.1, R93.1, U45.8 (VCCB), U51.8 (VCCB)
/CSI_DSI/CSI/CSI_RST: J12.21, U53.12 (1B1)
/CSI_DSI/CSI/I2C1_DTA_LVDS0: J12.18, R65.2, U45.6 (B1)
/CSI_DSI/CSI/I2C1_SCL: R66.2, U45.2 (A0)
/CSI_DSI/CSI/I2C1_SCL_LVDS0: J12.17, R64.2, U45.7 (B0)
/CSI_DSI/CSI/I2C1_SDA: R67.2, U45.3 (A1)
/CSI_DSI/CSI/I2C2_DTA_LVDS0: J13.18, R93.2, U51.6 (B1)
/CSI_DSI/CSI/I2C2_SCL: R94.2, U51.2 (A0)
/CSI_DSI/CSI/I2C2_SCL_LVDS0: J13.17, R92.2, U51.7 (B0)
/CSI_DSI/CSI/I2C2_SDA: R95.2, U51.3 (A1)
/CSI_DSI/CSI/MIPI_CSI_1_CLK+: J12.14, L9.3, U19.5 (I/O), U19.6 (I/O)
/CSI_DSI/CSI/MIPI_CSI_1_CLK-: J12.15, L9.4, U19.4 (I/O), U19.7 (I/O)
/CSI_DSI/CSI/MIPI_CSI_1_D0+: J12.11, L11.3, U44.2 (I/O), U44.9 (I/O)
/CSI_DSI/CSI/MIPI_CSI_1_D0-: J12.12, L11.4, U44.1 (I/O), U44.10 (I/O)
/CSI_DSI/CSI/MIPI_CSI_1_D1+: J12.8, L10.3, U44.5 (I/O), U44.6 (I/O)
/CSI_DSI/CSI/MIPI_CSI_1_D1-: J12.9, L10.4, U44.4 (I/O), U44.7 (I/O)
/CSI_DSI/CSI/MIPI_CSI_1_D2+: J12.5, L8.3, U23.2 (I/O), U23.9 (I/O)
/CSI_DSI/CSI/MIPI_CSI_1_D2-: J12.6, L8.4, U23.1 (I/O), U23.10 (I/O)
/CSI_DSI/CSI/MIPI_CSI_1_D3+: J12.2, L7.3, U23.5 (I/O), U23.6 (I/O)
/CSI_DSI/CSI/MIPI_CSI_1_D3-: J12.3, L7.4, U23.4 (I/O), U23.7 (I/O)
/CSI_DSI/CSI/MIPI_CSI_2_CLK+: J13.14, L12.3, U46.5 (I/O), U46.6 (I/O)
/CSI_DSI/CSI/MIPI_CSI_2_CLK-: J13.15, L12.4, U46.4 (I/O), U46.7 (I/O)
/CSI_DSI/CSI/MIPI_CSI_2_D0+: J13.11, L16.3, U48.2 (I/O), U48.9 (I/O)
/CSI_DSI/CSI/MIPI_CSI_2_D0-: J13.12, L16.4, U48.1 (I/O), U48.10 (I/O)
/CSI_DSI/CSI/MIPI_CSI_2_D1+: J13.8, L13.3, U48.5 (I/O), U48.6 (I/O)
/CSI_DSI/CSI/MIPI_CSI_2_D1-: J13.9, L13.4, U48.4 (I/O), U48.7 (I/O)
/CSI_DSI/CSI/MIPI_CSI_2_D2+: J13.5, L15.3, U47.2 (I/O), U47.9 (I/O)
/CSI_DSI/CSI/MIPI_CSI_2_D2-: J13.6, L15.4, U47.1 (I/O), U47.10 (I/O)
/CSI_DSI/CSI/MIPI_CSI_2_D3+: J13.2, L14.3, U47.5 (I/O), U47.6 (I/O)
/CSI_DSI/CSI/MIPI_CSI_2_D3-: J13.3, L14.4, U47.4 (I/O), U47.7 (I/O)
/CSI_DSI/CSI/con_rst: J13.21, U53.1 (1A1)
/CSI_DSI/CSI/mclk: J12.20, J13.20
CSI1_CLK_N: L9.1; also elsewhere on the board
CSI1_CLK_P: L9.2; also elsewhere on the board
CSI1_D0_N: L11.2; also elsewhere on the board
CSI1_D0_P: L11.1; also elsewhere on the board
CSI1_D1_N: L10.2; also elsewhere on the board
CSI1_D1_P: L10.1; also elsewhere on the board
CSI1_D2_N: L8.2; also elsewhere on the board
CSI1_D2_P: L8.1; also elsewhere on the board
CSI1_D3_N: L7.2; also elsewhere on the board
CSI1_D3_P: L7.1; also elsewhere on the board
CSI2_CLK_N: L12.1; also elsewhere on the board
CSI2_CLK_P: L12.2; also elsewhere on the board
CSI2_D0_N: L16.1; also elsewhere on the board
CSI2_D0_P: L16.2; also elsewhere on the board
CSI2_D1_N: L13.1; also elsewhere on the board
CSI2_D1_P: L13.2; also elsewhere on the board
CSI2_D2_N: L15.1; also elsewhere on the board
CSI2_D2_P: L15.2; also elsewhere on the board
CSI2_D3_N: L14.1; also elsewhere on the board
CSI2_D3_P: L14.2; also elsewhere on the board
CTRL_RESET: J12.19, J13.19
GND: C79.2, C80.2, C196.2, C197.2, J12.1, J12.4, J12.7, J12.10, J12.13, J12.16, J13.1, J13.4, J13.7, J13.10, J13.13, J13.16, U19.3 (GND), U19.8 (GND), U23.3 (GND), U23.8 (GND), U44.3 (GND), U44.8 (GND), U45.4 (GND), U46.3 (GND), U46.8 (GND), U47.3 (GND), U47.8 (GND), U48.3 (GND), U48.8 (GND), U51.4 (GND); also elsewhere on the board
unnamed: U53.8 (GND), U53.9 (GND)
